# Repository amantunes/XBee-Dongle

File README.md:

# XBee Dongle

This small USB-C dongle was developed with the objective of obtaining long range, relatively low bitrate communication with a rover or drone, as a way to transmit telemetry data to a computer or smartphone.

For this, a CP2102N USB-to-UART bridge was used. This bridge provides a small internal 100 mA 3.3V voltage regulator, which is used to power a Digi XBee 2.4 GHz communications module with an integrated chip antenna.

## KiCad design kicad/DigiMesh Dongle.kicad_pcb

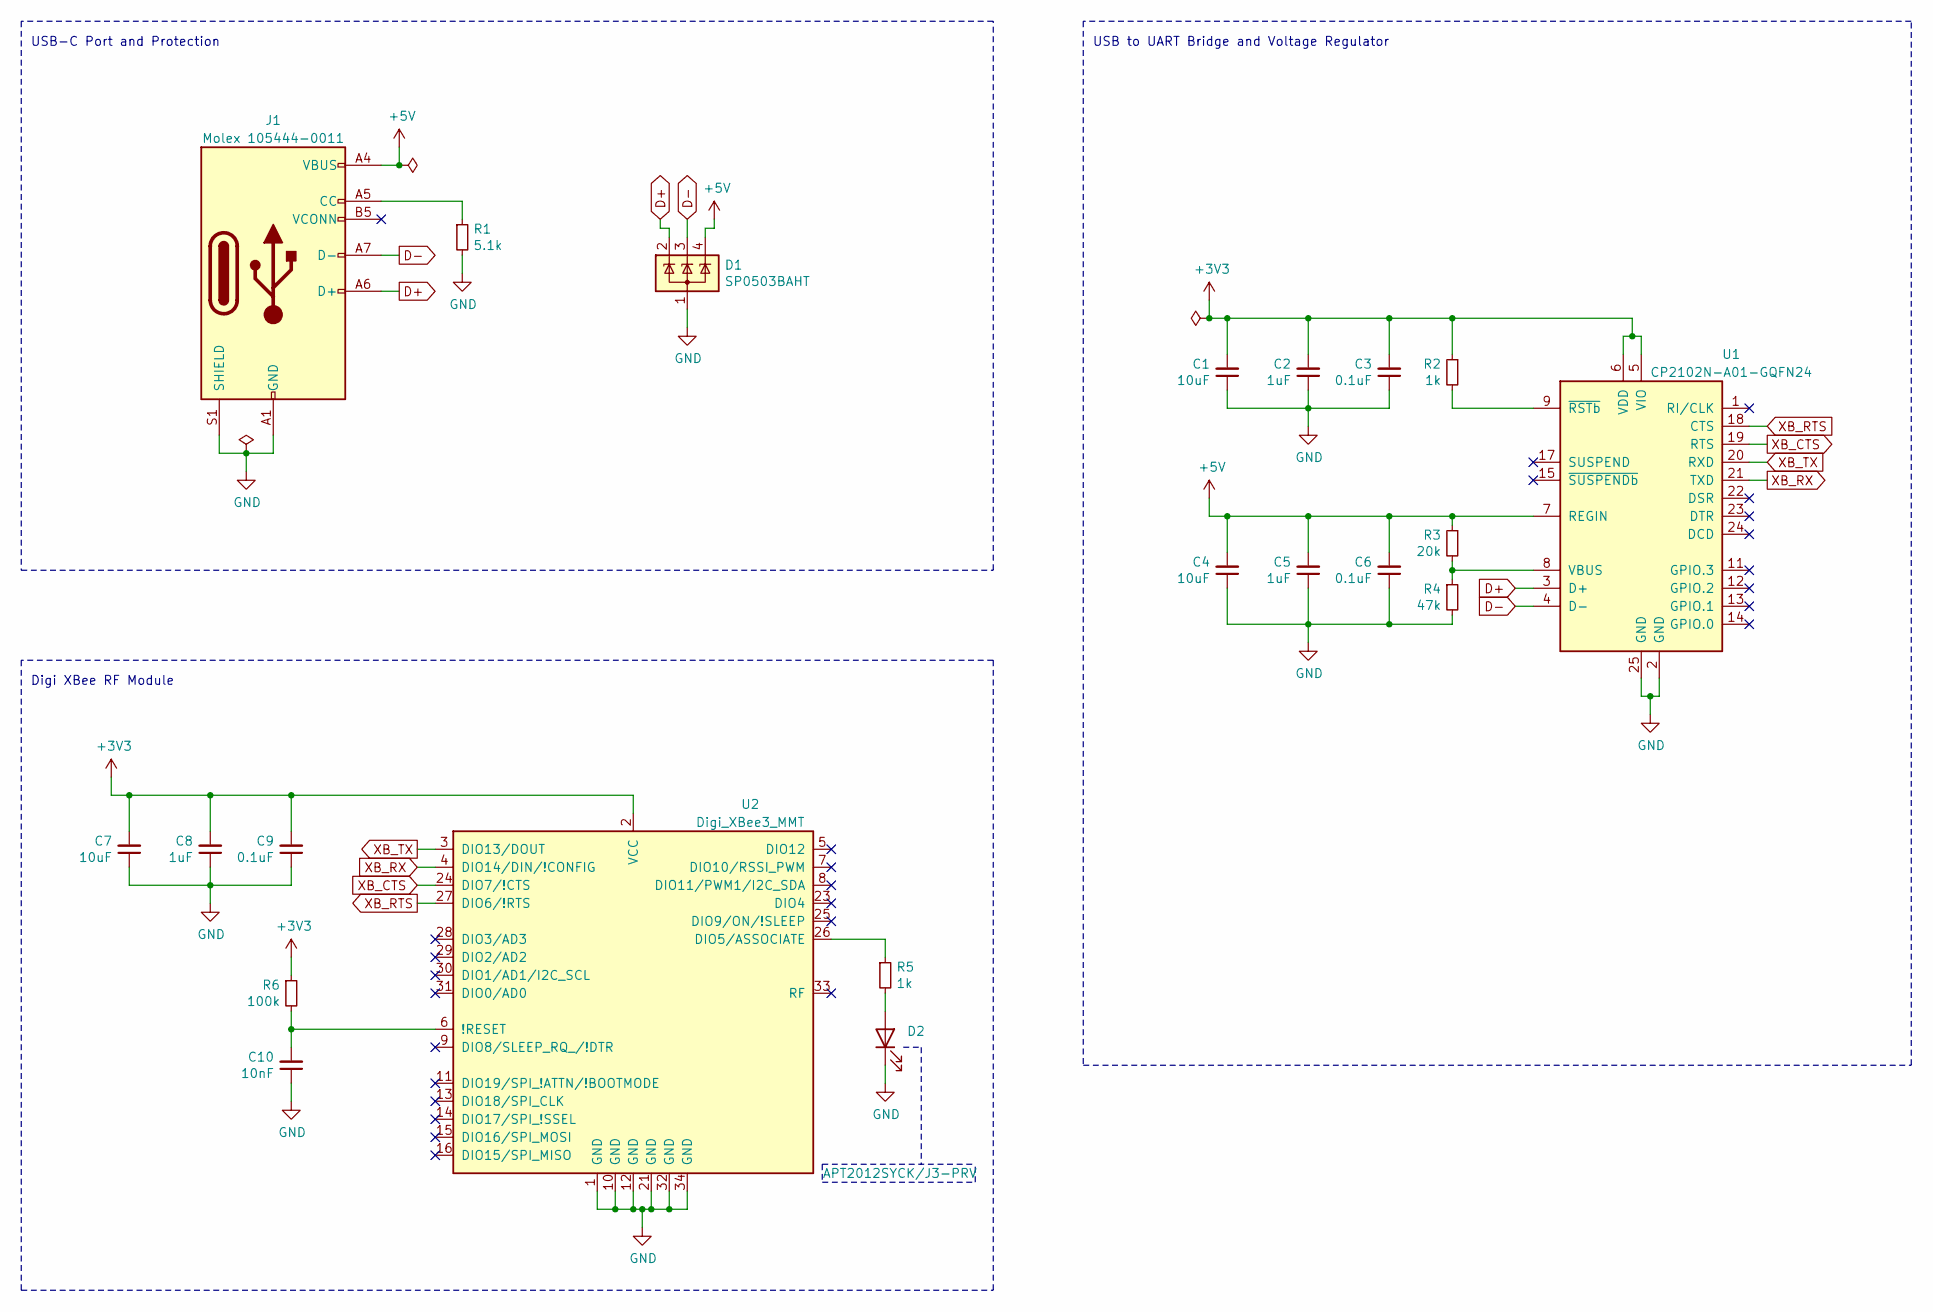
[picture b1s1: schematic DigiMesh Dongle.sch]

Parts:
C1, C4, C7: 10uF; C_0805_2012Metric_Pad1.18x1.45mm_HandSolder
C2, C5, C8: 1uF; C_0805_2012Metric_Pad1.18x1.45mm_HandSolder
C3, C6, C9: 0.1uF; C_0805_2012Metric_Pad1.18x1.45mm_HandSolder
C10: 10nF; C_0805_2012Metric_Pad1.18x1.45mm_HandSolder
D1: SP0503BAHT; SOT-143
D2: APT2012SYCK/J3-PRV; LED_0805_2012Metric_Pad1.15x1.40mm_HandSolder
J1: Molex 105444-0011; USB_C_Plug_Molex_105444
R1: 5.1k; R_0805_2012Metric_Pad1.20x1.40mm_HandSolder
R2, R5: 1k; R_0805_2012Metric_Pad1.20x1.40mm_HandSolder
R3: 20k; R_0805_2012Metric_Pad1.20x1.40mm_HandSolder
R4: 47k; R_0805_2012Metric_Pad1.20x1.40mm_HandSolder
R6: 100k; R_0805_2012Metric_Pad1.20x1.40mm_HandSolder
U1: CP2102N-A01-GQFN24; QFN-24-1EP_4x4mm_P0.5mm_EP2.6x2.6mm
U2: Digi_XBee3_MMT; Module_XCVR_XB3-24Z8CM-J

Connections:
+3V3: C1.2, C2.2, C3.2, C7.2, C8.2, C9.2, R2.1, R6.1, U1.5 (VIO), U1.6 (VDD), U2.2 (VCC)
+5V: C4.2, C5.2, C6.2, D1.4 (K), J1.A4 (VBUS), J1.A9 (VBUS), J1.B4 (VBUS), J1.B9 (VBUS), R3.1, U1.7 (REGIN)
D+: D1.2 (K), J1.A6 (D+), U1.3 (D+)
D-: D1.3 (K), J1.A7 (D-), U1.4 (D-)
GND: C1.1, C2.1, C3.1, C4.1, C5.1, C6.1, C7.1, C8.1, C9.1, C10.1, D1.1 (A), D2.1 (K), J1.A1 (GND), J1.A12 (GND), J1.B1 (GND), J1.B12 (GND), J1.S1 (SHIELD), R1.2, R4.2, U1.2 (GND), U1.25 (GND), U2.1 (GND), U2.10 (GND), U2.12 (GND), U2.21 (GND), U2.32 (GND), U2.34 (GND)
unnamed: C10.2, R6.2, U2.6 (!RESET)
unnamed: D2.2 (A), R5.2
unnamed: J1.A5 (CC), R1.1
unnamed: R2.2, U1.9 (~RSTb)
unnamed: R3.2, R4.1, U1.8 (VBUS)
unnamed: R5.1, U2.26 (DIO5/ASSOCIATE)
XB_CTS: U1.19 (RTS), U2.24 (DIO7/!CTS)
XB_RTS: U1.18 (CTS), U2.27 (DIO6/!RTS)
XB_RX: U1.21 (TXD), U2.4 (DIO14/DIN/!CONFIG)
XB_TX: U1.20 (RXD), U2.3 (DIO13/DOUT)

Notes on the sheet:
USB-C Port and Protection
USB to UART Bridge and Voltage Regulator
Digi XBee RF Module

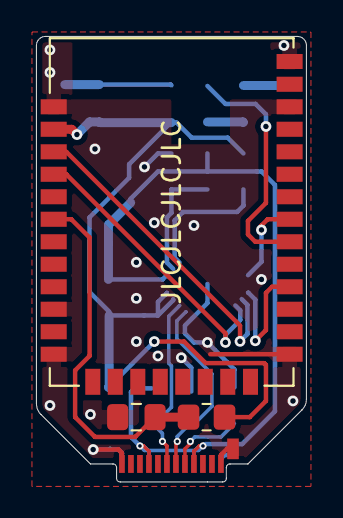
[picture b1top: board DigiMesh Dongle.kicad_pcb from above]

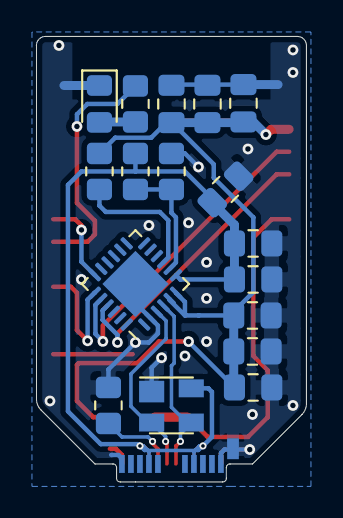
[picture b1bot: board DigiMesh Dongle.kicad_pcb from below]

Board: 2 copper layers, 15.0 x 24.8 mm, 21 parts (17 on the bottom side), 15 nets.

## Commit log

2021-08-14 Initial v1.0 Upload
2021-08-15 v1.0 Files
